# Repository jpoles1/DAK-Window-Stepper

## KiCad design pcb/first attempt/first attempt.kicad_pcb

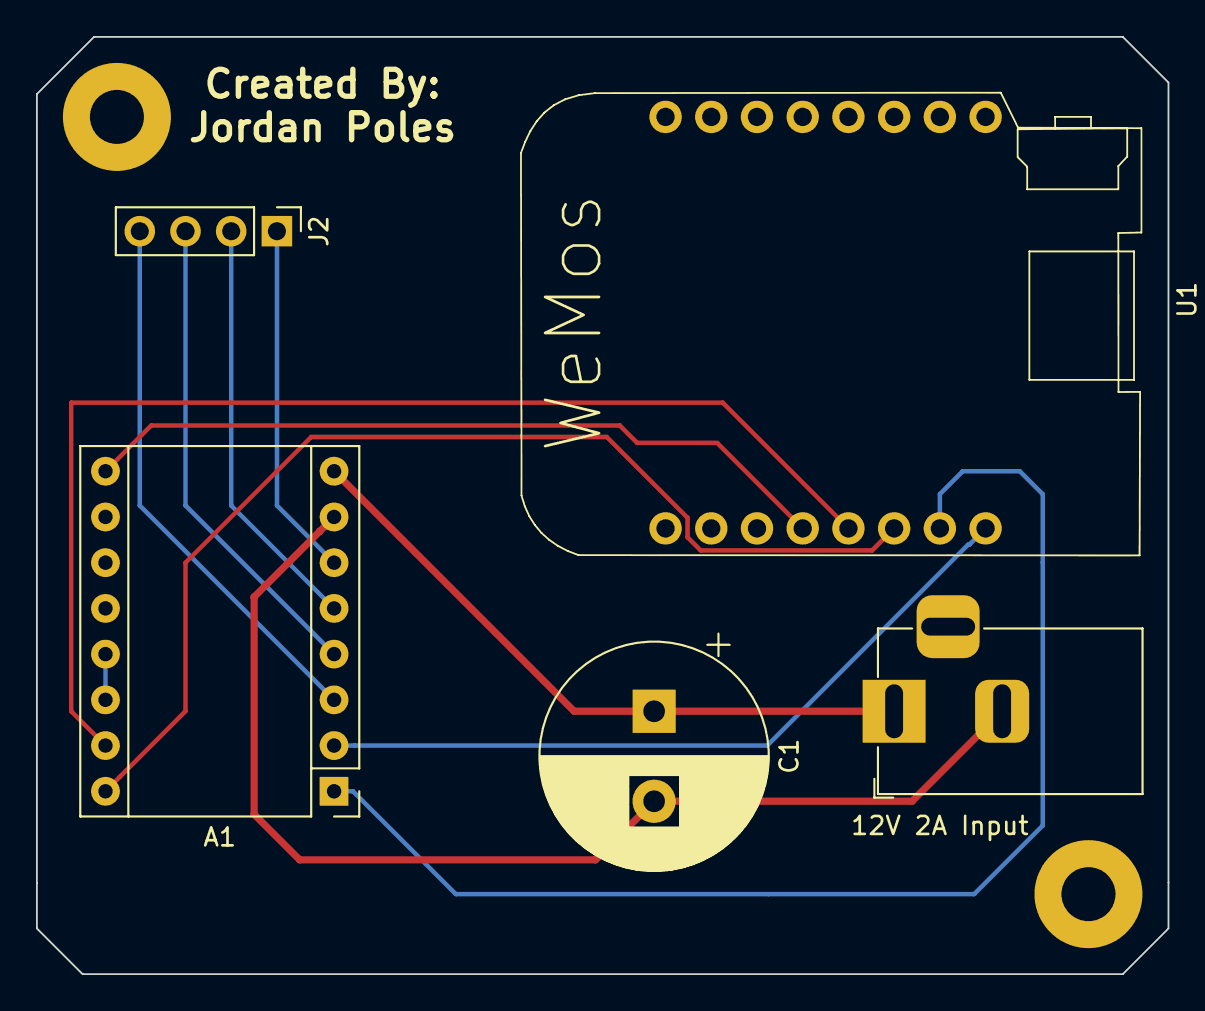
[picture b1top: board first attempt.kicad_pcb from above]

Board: 2 copper layers, 62.9 x 52.1 mm, 5 parts (0 on the bottom side), 12 nets.

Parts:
12V 2A Input: Barrel Jack; BarrelJack_Horizontal
A1: A4988 Stepper Driver; Pololu_Breakout-16_15.2x20.3mm
C1: 100uF CP; CP_Radial_D12.5mm_P5.00mm
J2: Stepper; PinHeader_1x04_P2.54mm_Vertical
U1: WeMos D1 Mini; D1_mini_board

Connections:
unnamed: A1.1, U1.2
unnamed: A1.2, U1.1
unnamed: A1.3, J2.4
unnamed: A1.4, J2.3
unnamed: A1.5, J2.2
unnamed: A1.6, J2.1
unnamed: 12V 2A Input.2, A1.7, C1.2
unnamed: 12V 2A Input.1, A1.8, C1.1
unnamed: A1.9, U1.5
unnamed: A1.13, A1.14
unnamed: A1.15, U1.4
unnamed: A1.16, U1.3

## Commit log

2018-10-03 Got stepper setup! And PCB drafted!
